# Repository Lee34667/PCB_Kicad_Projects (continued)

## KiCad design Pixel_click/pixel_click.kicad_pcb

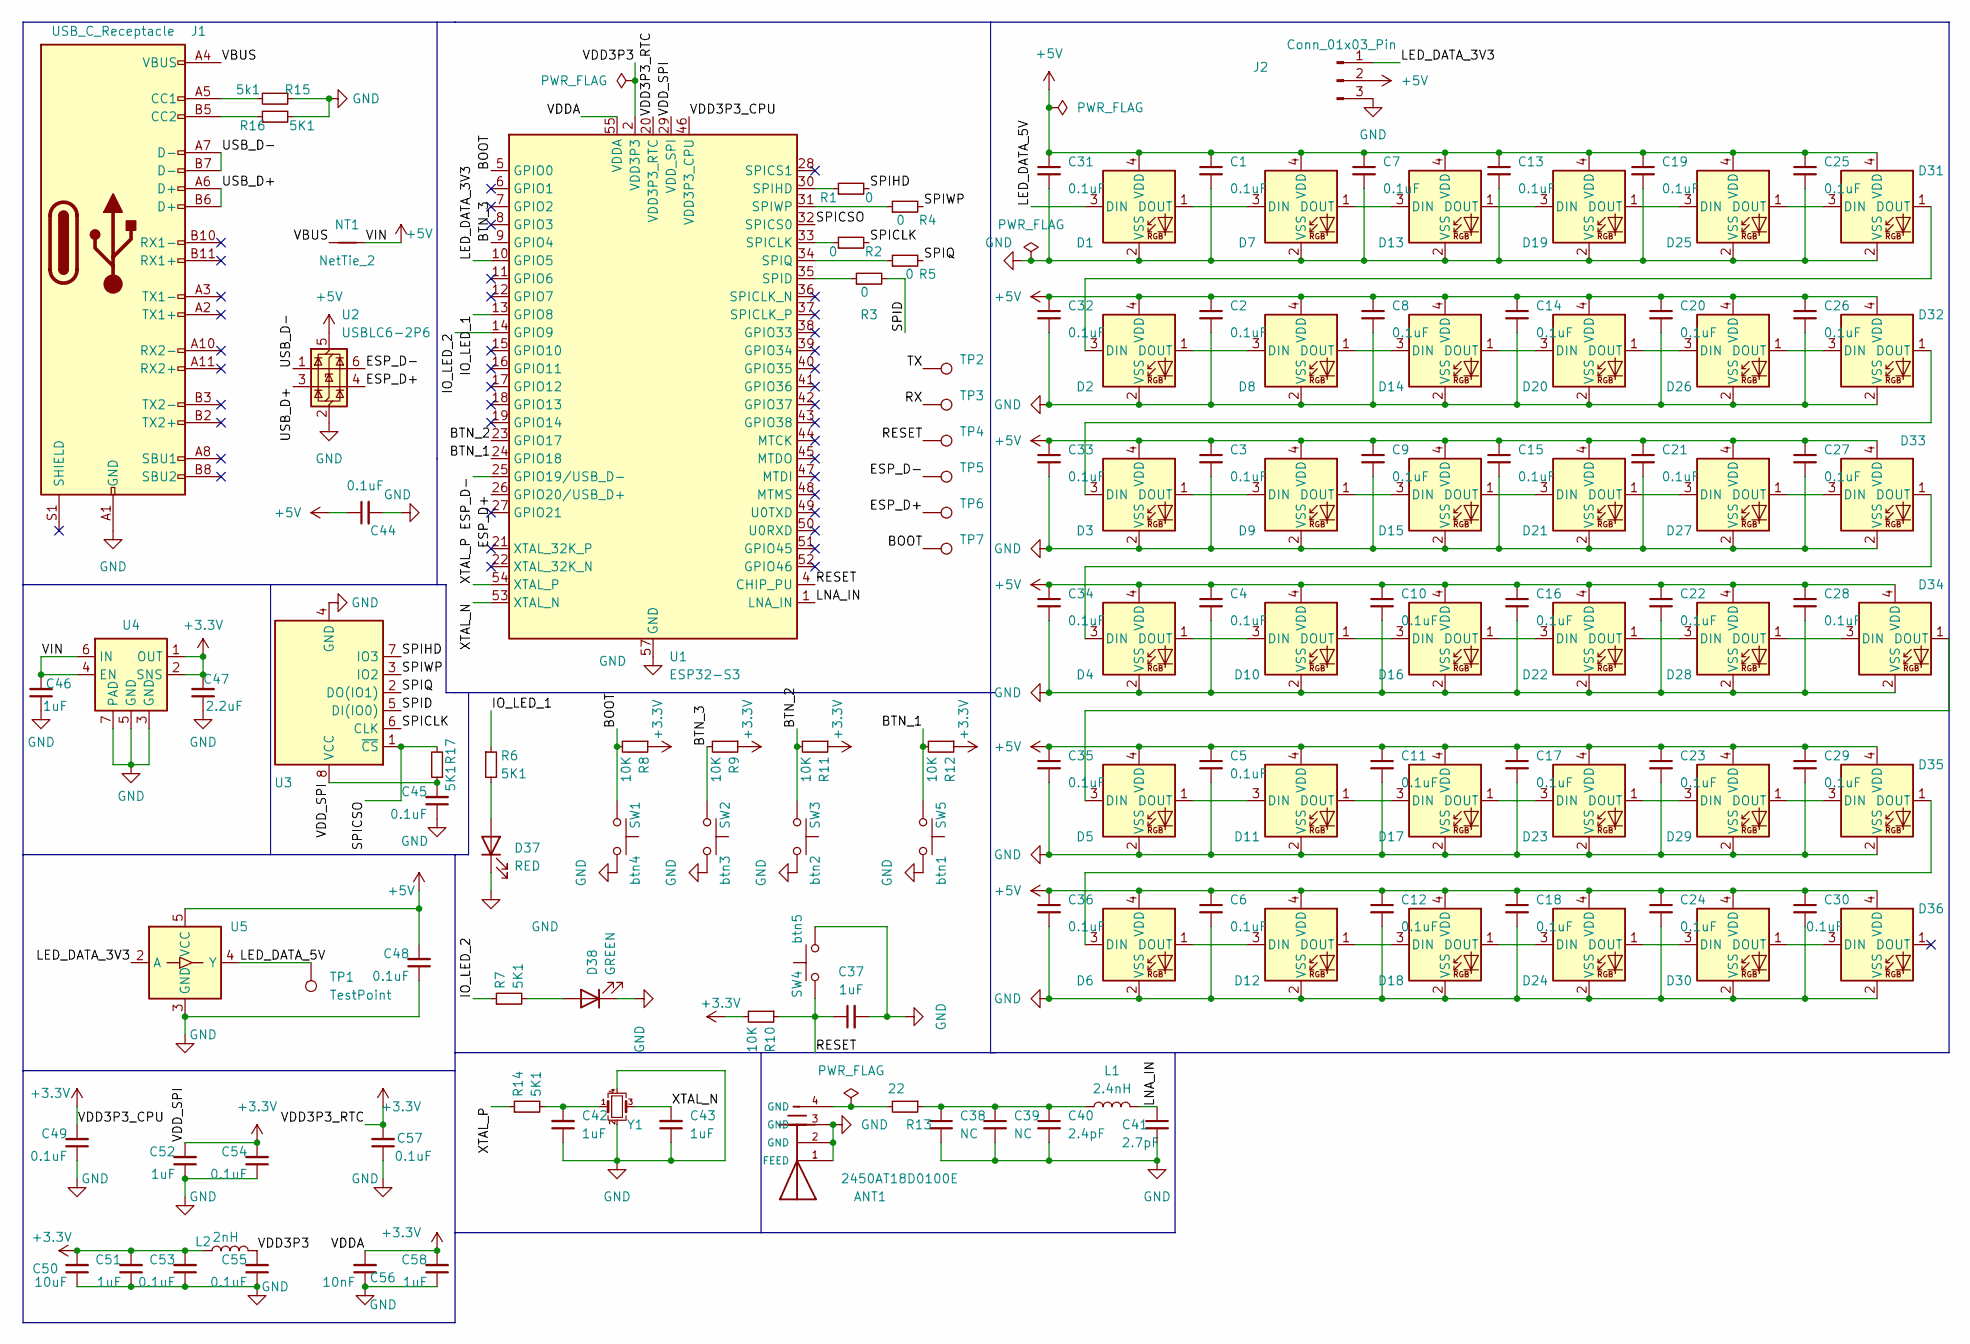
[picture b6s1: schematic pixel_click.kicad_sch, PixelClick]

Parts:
ANT1: 2450AT18D0100E; DFN320X160X120-4RN
C1, C2, C3, C4, C5, C6, C7, C8, C9, C10, C11, C12, C13, C14, C15, C16, C17, C18, C19, C20, C21, C22, C23, C24, C25, C26, C27, C28, C29, C30, C31, C32, C33, C34, C35, C36, C44, C45, C48, C49, C53, C54, C55, C57: 0.1uF; C_0201_0603Metric
C37, C42, C43, C46, C51, C52, C58: 1uF; C_0201_0603Metric
C38, C39: NC; C_0201_0603Metric
C40: 2.4pF; C_0201_0603Metric
C41: 2.7pF; C_0201_0603Metric
C47: 2.2uF; C_0201_0603Metric
C50: 10uF; C_0201_0603Metric
C56: 10nF; C_0201_0603Metric
D1, D2, D3, D4, D5, D6, D7, D8, D9, D10, D11, D12, D13, D14, D15, D16, D17, D18, D19, D20, D21, D22, D23, D24, D25, D26, D27, D28, D29, D30, D31, D32, D33, D34, D35, D36: SK6805; LED_SK6805_PLCC4_2.4x2.7mm_P1.3mm
D37: RED; LED_0201_0603Metric
D38: GREEN; LED_0402_1005Metric
J1: USB_C_Receptacle; USB_C_Receptacle_Amphenol_12401548E4-2A
J2: Conn_01x03_Pin; PinHeader_1x03_P1.27mm_Horizontal
L1: 2.4nH; L_0201_0603Metric
L2: 2nH; L_0201_0603Metric
NT1: NetTie_2; NetTie-2_SMD_Pad0.5mm
R1, R2, R3, R4, R5: 0; R_0201_0603Metric
R6, R7, R14, R16, R17: 5K1; R_0201_0603Metric
R8, R9, R10, R11, R12: 10K; R_0201_0603Metric
R13: 22; R_0201_0603Metric
R15: 5k1; R_0201_0603Metric
SW1: btn4; SW_Tactile_SPST_Angled_PTS645Vx39-2LFS
SW2: btn3; SW_Tactile_SPST_Angled_PTS645Vx39-2LFS
SW3: btn2; SW_Tactile_SPST_Angled_PTS645Vx39-2LFS
SW4: btn5; SW_Tactile_SPST_Angled_PTS645Vx39-2LFS
SW5: btn1; SW_Tactile_SPST_Angled_PTS645Vx39-2LFS
TP1: TestPoint; TestPoint_Bridge_Pitch2.0mm_Drill0.7mm
TP2, TP3, TP4, TP5, TP6, TP7: TestPoint
U1: ESP32-S3; QFN-56-1EP_7x7mm_P0.4mm_EP4x4mm
U2: USBLC6-2P6; SOT-666
U3: W25Q128JVS; SOIC-8_5.23x5.23mm_P1.27mm
U4: TLV76733DRVx; WSON-6-1EP_2x2mm_P0.65mm_EP1x1.6mm_ThermalVias
U5: SN74LV1T34DBV; SOT-23-5
Y1: Crystal_GND24_Small; XTAL_ECS-400-10-37B2-CKY-TR

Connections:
+3.3V: C45.2, C47.2, C49.2, C50.2, C51.2, C52.2, C53.2, C54.2, C56.2, C57.2, C58.2, L2.1, R8.1, R9.1, R10.2, R11.1, R12.1, R17.1, U1.20 (VDD3P3_RTC), U1.29 (VDD_SPI), U1.46 (VDD3P3_CPU), U1.55 (VDDA), U1.56 (VDDA), U3.8 (VCC), U4.1 (OUT), U4.2 (SNS)
+5V: C1.1, C2.1, C3.1, C4.1, C5.1, C6.1, C7.1, C8.1, C9.1, C10.1, C11.1, C12.1, C13.1, C14.1, C15.1, C16.1, C17.1, C18.1, C19.1, C20.1, C21.1, C22.1, C23.1, C24.1, C25.1, C26.1, C27.1, C28.1, C29.1, C30.1, C31.1, C32.1, C33.1, C34.1, C35.1, C36.1, C44.1, C46.2, C48.2, D1.4 (VDD), D2.4 (VDD), D3.4 (VDD), D4.4 (VDD), D5.4 (VDD), D6.4 (VDD), D7.4 (VDD), D8.4 (VDD), D9.4 (VDD), D10.4 (VDD), D11.4 (VDD), D12.4 (VDD), D13.4 (VDD), D14.4 (VDD), D15.4 (VDD), D16.4 (VDD), D17.4 (VDD), D18.4 (VDD), D19.4 (VDD), D20.4 (VDD), D21.4 (VDD), D22.4 (VDD), D23.4 (VDD), D24.4 (VDD), D25.4 (VDD), D26.4 (VDD), D27.4 (VDD), D28.4 (VDD), D29.4 (VDD), D30.4 (VDD), D31.4 (VDD), D32.4 (VDD), D33.4 (VDD), D34.4 (VDD), D35.4 (VDD), D36.4 (VDD), J2.2, NT1.2, U2.5 (VBUS), U4.4 (EN), U4.6 (IN), U5.5 (VCC)
/BOOT: R8.2, SW1.1, TP7.1, U1.5 (GPIO0)
/BTN_1: R12.2, SW5.1, U1.24 (GPIO18), U1.27 (GPIO18)
/BTN_2: R11.2, SW3.1, U1.23 (GPIO17)
/BTN_3: R9.2, SW2.1, U1.9 (GPIO4), U1.28 (GP1O4)
/ESP_D+: TP6.1, U1.26 (GPIO20/USB_D+), U2.4 (I/O2)
/ESP_D-: TP5.1, U1.25 (GPIO19/USB_D-), U2.6 (I/O1)
/IO_LED_1: R6.1, U1.13 (GPIO8)
/IO_LED_2: R7.1, U1.14 (GPIO9)
/LED_DATA_3V3: J2.1, U1.10 (GPIO5), U5.2 (A)
/LED_DATA_5V: D1.3 (DIN), TP1.1, U5.4 (Y)
/LNA_IN: C41.1, L1.2, U1.1 (LNA_IN)
/RESET: C37.1, R10.1, SW4.1, TP4.1, U1.4 (CHIP_PU)
/SPICLK: R2.2, U3.6 (CLK)
/SPICSO: R17.2, U1.32 (SPICS0), U3.1 (~CS)
/SPID: R3.2, U3.5 (DI(IO0))
/SPIHD: R1.2, U3.7 (IO3)
/SPIQ: R5.2, U3.2 (DO(IO1))
/SPIWP: R4.2, U3.3 (IO2)
/USB_D+: J1.A6 (D+), J1.B6 (D+), U2.3 (I/O2)
/USB_D-: J1.A7 (D-), J1.B7 (D-), U2.1 (I/O1)
/VBUS: J1.A4 (VBUS), J1.A9 (VBUS), J1.B4 (VBUS), J1.B9 (VBUS), NT1.1
/VDD3P3: C55.2, L2.2, U1.2 (VDD3P3), U1.3 (VDD3P3)
/XTAL_N: C43.2, U1.53 (XTAL_N), Y1.3
/XTAL_P: R14.1, U1.54 (XTAL_P)
GND: ANT1.1 (FEED), ANT1.2 (GND), ANT1.3 (GND), C1.2, C2.2, C3.2, C4.2, C5.2, C6.2, C7.2, C8.2, C9.2, C10.2, C11.2, C12.2, C13.2, C14.2, C15.2, C16.2, C17.2, C18.2, C19.2, C20.2, C21.2, C22.2, C23.2, C24.2, C25.2, C26.2, C27.2, C28.2, C29.2, C30.2, C31.2, C32.2, C33.2, C34.2, C35.2, C36.2, C37.2, C38.2, C39.2, C40.2, C41.2, C42.1, C43.1, C44.2, C45.1, C46.1, C47.1, C48.1, C49.1, C50.1, C51.1, C52.1, C53.1, C54.1, C55.1, C56.1, C57.1, C58.1, D1.2 (VSS), D2.2 (VSS), D3.2 (VSS), D4.2 (VSS), D5.2 (VSS), D6.2 (VSS), D7.2 (VSS), D8.2 (VSS), D9.2 (VSS), D10.2 (VSS), D11.2 (VSS), D12.2 (VSS), D13.2 (VSS), D14.2 (VSS), D15.2 (VSS), D16.2 (VSS), D17.2 (VSS), D18.2 (VSS), D19.2 (VSS), D20.2 (VSS), D21.2 (VSS), D22.2 (VSS), D23.2 (VSS), D24.2 (VSS), D25.2 (VSS), D26.2 (VSS), D27.2 (VSS), D28.2 (VSS), D29.2 (VSS), D30.2 (VSS), D31.2 (VSS), D32.2 (VSS), D33.2 (VSS), D34.2 (VSS), D35.2 (VSS), D36.2 (VSS), D37.1 (K), D38.1 (K), J1.A1 (GND), J1.A12 (GND), J1.B1 (GND), J1.B12 (GND), J2.3, R15.1, R16.2, SW1.2, SW2.2, SW3.2, SW4.2, SW5.2, U1.57 (GND), U2.2 (GND), U3.4 (GND), U4.3 (GND), U4.5 (GND), U4.7 (PAD), U5.3 (GND), Y1.2, Y1.4
unnamed: ANT1.4 (GND), R13.2
unnamed: C38.1, C39.1, C40.1, L1.1, R13.1
unnamed: C42.2, R14.2, Y1.1
unnamed: D1.1 (DOUT), D7.3 (DIN)
unnamed: D2.3 (DIN), D31.1 (DOUT)
unnamed: D2.1 (DOUT), D8.3 (DIN)
unnamed: D3.3 (DIN), D32.1 (DOUT)
unnamed: D3.1 (DOUT), D9.3 (DIN)
unnamed: D4.1 (DOUT), D10.3 (DIN)
unnamed: D10.1 (DOUT), D16.3 (DIN)
unnamed: D5.1 (DOUT), D11.3 (DIN)
unnamed: D11.1 (DOUT), D17.3 (DIN)
unnamed: D6.1 (DOUT), D12.3 (DIN)
unnamed: D12.1 (DOUT), D18.3 (DIN)
unnamed: D7.1 (DOUT), D13.3 (DIN)
unnamed: D13.1 (DOUT), D19.3 (DIN)
unnamed: D8.1 (DOUT), D14.3 (DIN)
unnamed: D14.1 (DOUT), D20.3 (DIN)
unnamed: D9.1 (DOUT), D15.3 (DIN)
unnamed: D15.1 (DOUT), D21.3 (DIN)
unnamed: D16.1 (DOUT), D22.3 (DIN)
unnamed: D17.1 (DOUT), D23.3 (DIN)
unnamed: D18.1 (DOUT), D24.3 (DIN)
unnamed: D19.1 (DOUT), D25.3 (DIN)
unnamed: D20.1 (DOUT), D26.3 (DIN)
unnamed: D21.1 (DOUT), D27.3 (DIN)
unnamed: D22.1 (DOUT), D28.3 (DIN)
unnamed: D23.1 (DOUT), D29.3 (DIN)
unnamed: D24.1 (DOUT), D30.3 (DIN)
unnamed: D25.1 (DOUT), D31.3 (DIN)
unnamed: D26.1 (DOUT), D32.3 (DIN)
unnamed: D27.1 (DOUT), D33.3 (DIN)
unnamed: D28.1 (DOUT), D34.3 (DIN)
unnamed: D29.1 (DOUT), D35.3 (DIN)
unnamed: D30.1 (DOUT), D36.3 (DIN)
unnamed: D4.3 (DIN), D33.1 (DOUT)
unnamed: D5.3 (DIN), D34.1 (DOUT)
unnamed: D6.3 (DIN), D35.1 (DOUT)
unnamed: D37.2 (A), R6.2
unnamed: D38.2 (A), R7.2
unnamed: J1.A5 (CC1), R15.2
unnamed: J1.B5 (CC2), R16.1
unnamed: R2.1, U1.33 (SPICLK)
unnamed: R3.1, U1.35 (SPID)
unnamed: R1.1, U1.30 (SPIHD)
unnamed: R5.1, U1.34 (SPIQ)
unnamed: R4.1, U1.31 (SPIWP)

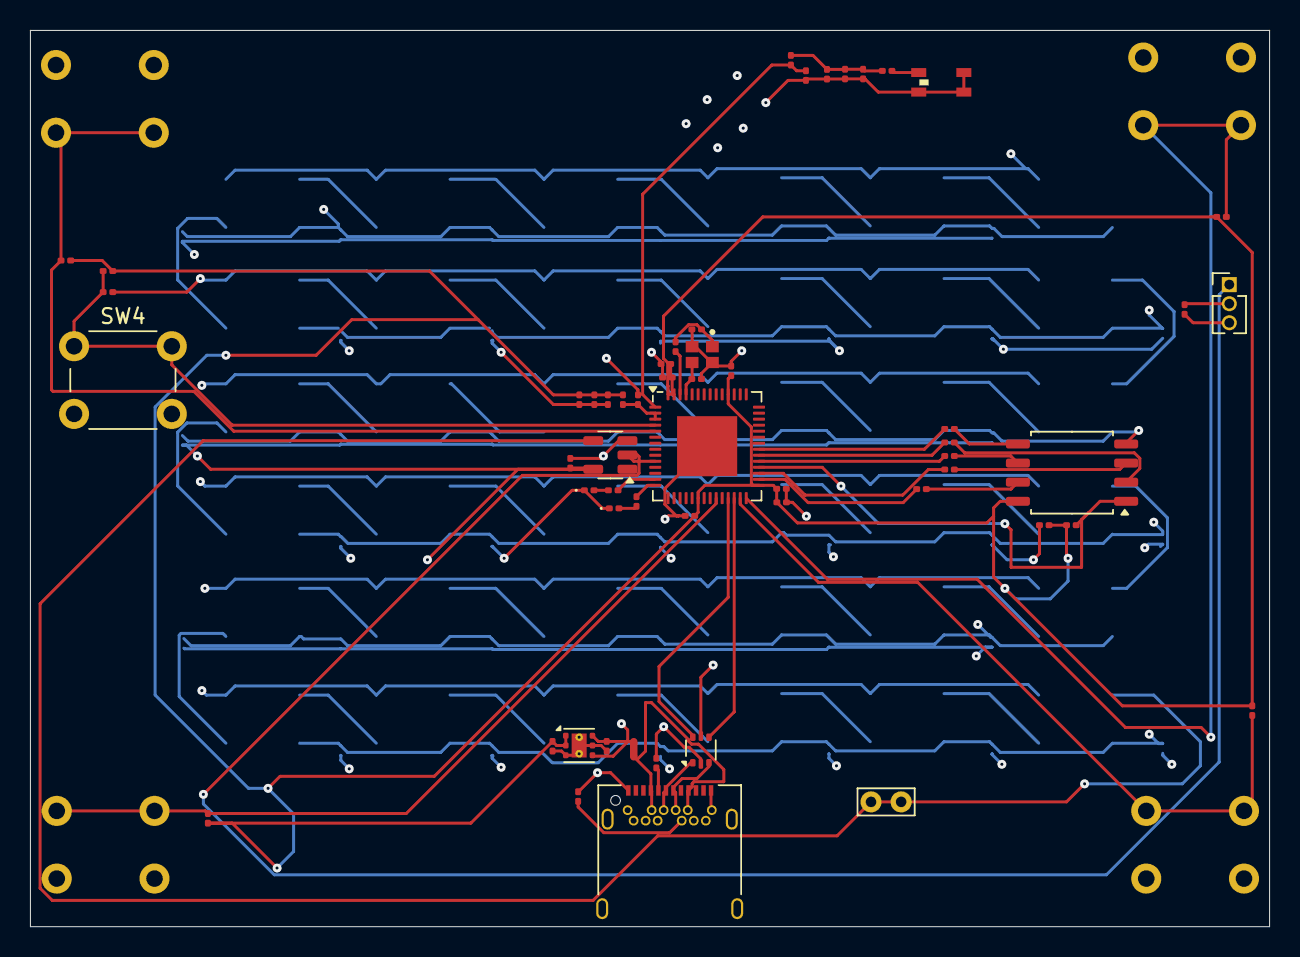
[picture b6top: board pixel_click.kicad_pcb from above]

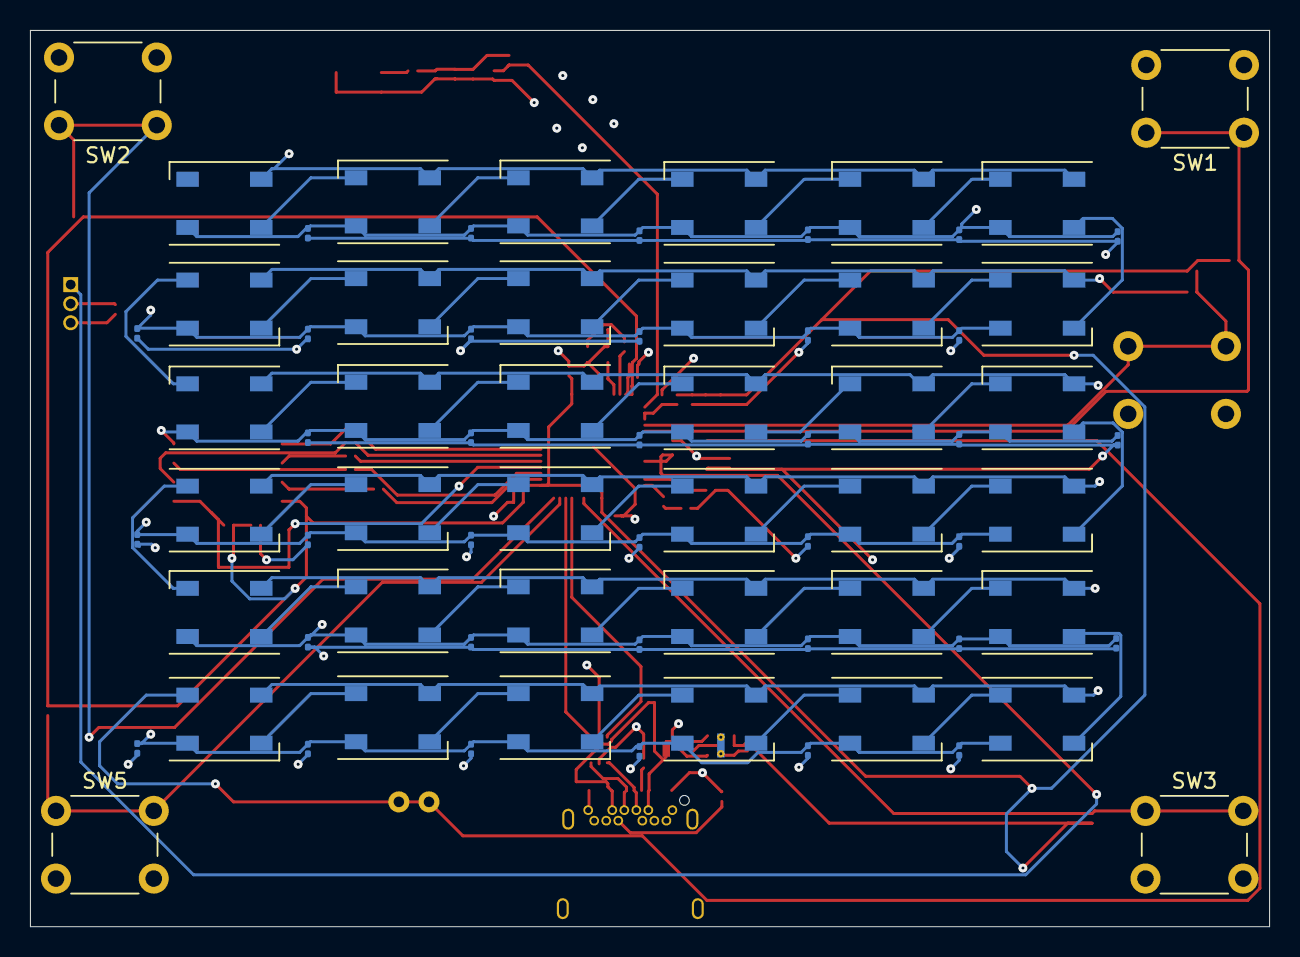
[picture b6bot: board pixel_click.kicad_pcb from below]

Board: 4 copper layers, 82.4 x 59.6 mm, 131 parts (76 on the bottom side), 74 nets.

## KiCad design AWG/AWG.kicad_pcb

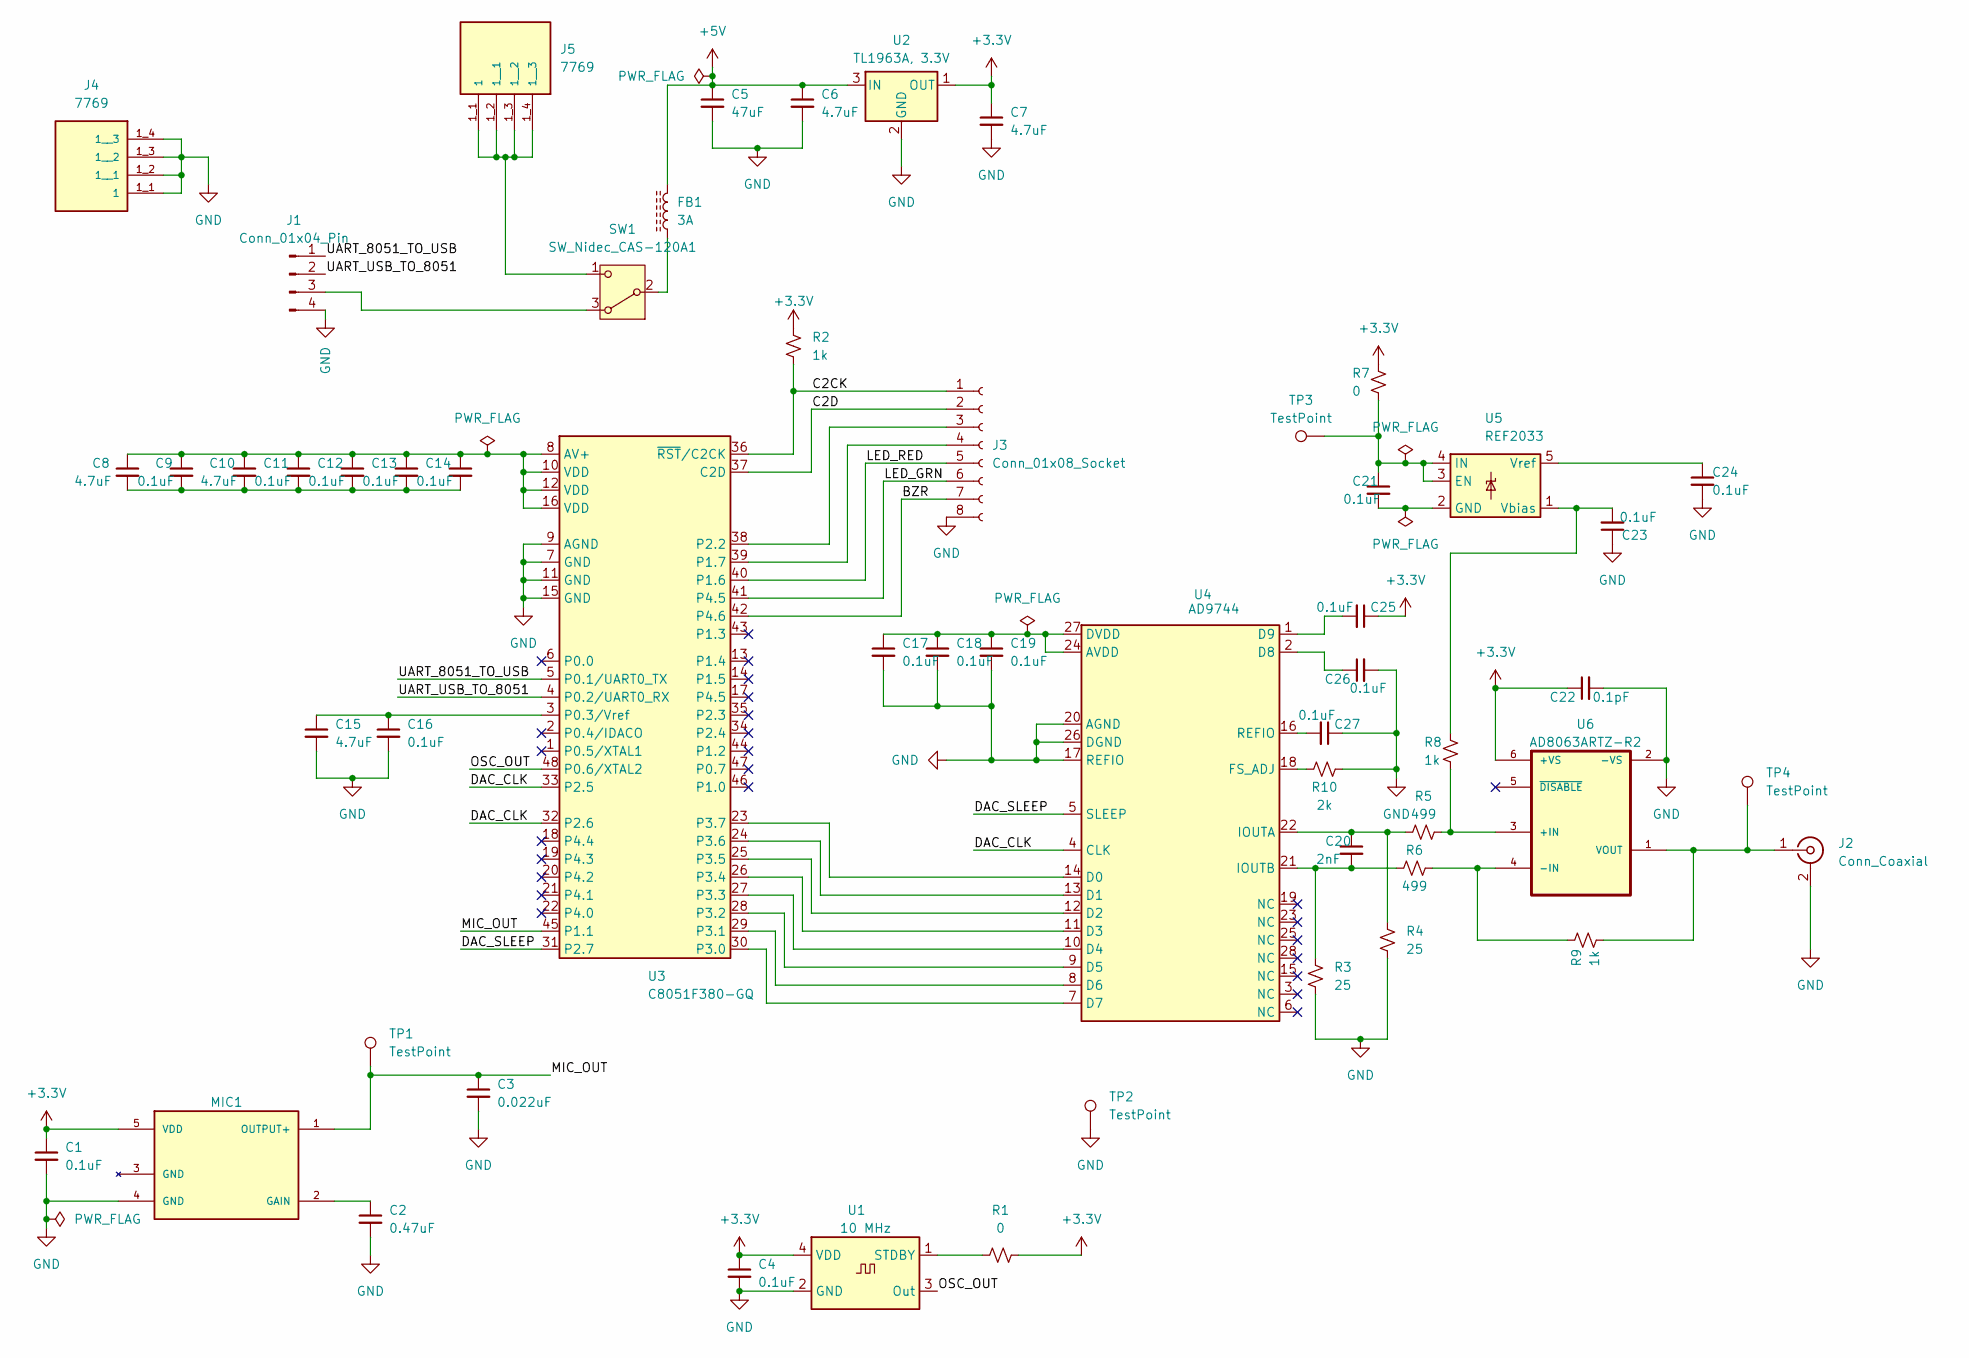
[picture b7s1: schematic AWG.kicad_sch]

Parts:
C1, C4, C9, C11, C12, C13, C14, C16, C17, C18, C19, C21, C23, C24, C25, C26, C27: 0.1uF; C_0805_2012Metric
C2: 0.47uF; C_0805_2012Metric
C3: 0.022uF; C_0805_2012Metric
C5: 47uF; CP_EIA-3528-12_Kemet-T
C6: 4.7uF; CP_EIA-3528-12_Kemet-T
C7, C8, C10, C15: 4.7uF; C_0805_2012Metric
C20: 2nF; C_0805_2012Metric
C22: 0.1pF; C_0805_2012Metric
FB1: 3A; L_Ferrocore_DLG-0302
J1: Conn_01x04_Pin; PinHeader_1x04_P2.00mm_Horizontal
J2: Conn_Coaxial; SMB_Jack_Vertical
J3: Conn_01x08_Socket; PinSocket_1x08_P2.00mm_Horizontal
J4, J5: 7769; KEYSTONE_7769; PARTREV B
MIC1: ICS-40618; MIC_ICS-40618
R1, R7: 0; R_0603_1608Metric_Pad0.98x0.95mm_HandSolder
R2, R8, R9: 1k; R_0603_1608Metric_Pad0.98x0.95mm_HandSolder
R3, R4: 25; R_0603_1608Metric_Pad0.98x0.95mm_HandSolder
R5, R6: 499; R_0603_1608Metric_Pad0.98x0.95mm_HandSolder
R10: 2k; R_0603_1608Metric_Pad0.98x0.95mm_HandSolder
SW1: SW_Nidec_CAS-120A1; Nidec_Copal_CAS-120A
TP1, TP2, TP3, TP4: TestPoint; TestPoint_Loop_D2.50mm_Drill1.0mm
U1: 10 MHz; Oscillator_SMD_Abracon_ASDMB-4Pin_2.5x2.0mm
U2: TL1963A, 3.3V; SOT-89-3
U3: C8051F380-GQ; TQFP-48_7x7mm_P0.5mm
U4: AD9744; TSSOP-28_4.4x9.7mm_P0.65mm
U5: REF2033; SOT-23-5
U6: AD8063ARTZ-R2; SOT95P280X145-6

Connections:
+3.3V: C1.1, C4.1, C7.1, C22.1, C25.1, MIC1.5 (VDD), R1.2, R2.1, R7.1, U1.4 (VDD), U2.1 (OUT), U6.6 (+VS)
+5V: C5.1, C6.1, FB1.2, U2.3 (IN)
/BZR: J3.7, U3.42 (P4.6)
/C2CK: J3.1, R2.2, U3.36 (~RST/C2CK)
/C2D: J3.2, U3.37 (C2D)
/DAC_CLK: U3.32 (P2.6), U3.33 (P2.5), U4.4 (CLK)
/DAC_SLEEP: U3.31 (P2.7), U4.5 (SLEEP)
/LED_GRN: J3.6, U3.41 (P4.5)
/LED_RED: J3.5, U3.40 (P1.6)
/MIC_OUT: C3.1, MIC1.1 (OUTPUT+), TP1.1, U3.45 (P1.1)
/OSC_OUT: U1.3 (Out), U3.48 (P0.6/XTAL2)
/UART_8051_TO_USB: J1.1, U3.5 (P0.1/UART0_TX)
/UART_USB_TO_8051: J1.2, U3.4 (P0.2/UART0_RX)
GND: C1.2, C2.2, C3.2, C4.2, C5.2, C6.2, C7.2, C15.2, C16.2, C17.2, C18.2, C19.2, C22.2, C23.1, C24.2, C26.2, C27.1, J1.4, J2.2 (Ext), J3.8, J4.1_1 (1), J4.1_2 (1__1), J4.1_3 (1__2), J4.1_4 (1__3), MIC1.4 (GND), R3.2, R4.2, R10.1, TP2.1, U1.2 (GND), U2.2 (GND), U3.7 (GND), U3.9 (AGND), U3.11 (GND), U3.15 (GND), U4.17 (REFIO), U4.20 (AGND), U4.26 (DGND), U6.2 (-VS)
unnamed: C8.2, C9.2, C10.2, C11.2, C12.2, C13.2, C14.2
unnamed: C27.2, U4.16 (REFIO)
unnamed: J1.3, SW1.3 (A)
unnamed: J2.1 (In), R9.2, TP4.1, U6.1 (VOUT)
unnamed: J3.3, U3.38 (P2.2)
unnamed: J3.4, U3.39 (P1.7)
unnamed: J5.1_1 (1), J5.1_2 (1__1), J5.1_3 (1__2), J5.1_4 (1__3), SW1.1 (C)
unnamed: C2.1, MIC1.2 (GAIN)
unnamed: FB1.1, SW1.2 (B)
unnamed: R1.1, U1.1 (STDBY)
unnamed: C8.1, C9.1, C10.1, C11.1, C12.1, C13.1, C14.1, U3.8 (AV+), U3.10 (VDD), U3.12 (VDD), U3.16 (VDD)
unnamed: C15.1, C16.1, U3.3 (P0.3/Vref)
unnamed: U3.30 (P3.0), U4.7 (D7)
unnamed: U3.29 (P3.1), U4.8 (D6)
unnamed: U3.28 (P3.2), U4.9 (D5)
unnamed: U3.27 (P3.3), U4.10 (D4)
unnamed: U3.26 (P3.4), U4.11 (D3)
unnamed: U3.25 (P3.5), U4.12 (D2)
unnamed: U3.24 (P3.6), U4.13 (D1)
unnamed: U3.23 (P3.7), U4.14 (D0)
unnamed: C17.1, C18.1, C19.1, U4.24 (AVDD), U4.27 (DVDD)
unnamed: C26.1, U4.2 (D8)
unnamed: C25.2, U4.1 (D9)
unnamed: R10.2, U4.18 (FS_ADJ)
unnamed: C20.1, R4.1, R5.1, U4.22 (IOUTA)
unnamed: C20.2, R3.1, R6.1, U4.21 (IOUTB)
unnamed: C21.1, R7.2, TP3.1, U5.3 (EN), U5.4 (IN)
unnamed: C21.2, U5.2 (GND)
unnamed: C23.2, R8.1, U5.1 (Vbias)
unnamed: C24.1, U5.5 (Vref)
unnamed: R5.2, R8.2, U6.3 (+IN)
unnamed: R6.2, R9.1, U6.4 (-IN)

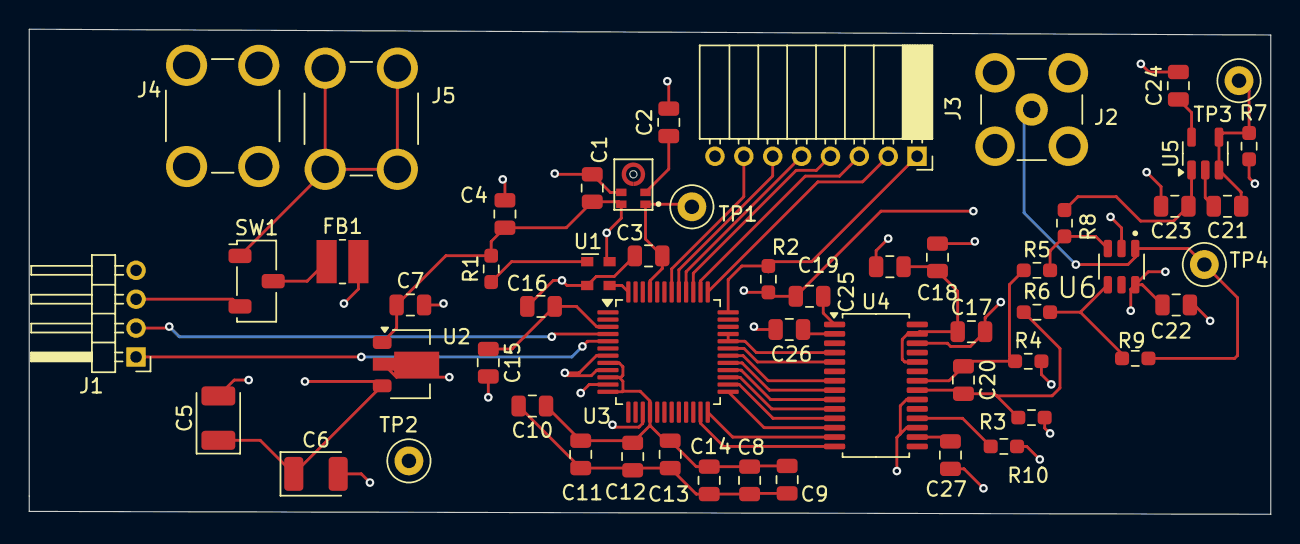
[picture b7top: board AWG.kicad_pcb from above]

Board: 4 copper layers, 86.0 x 33.6 mm, 55 parts (0 on the bottom side), 46 nets.

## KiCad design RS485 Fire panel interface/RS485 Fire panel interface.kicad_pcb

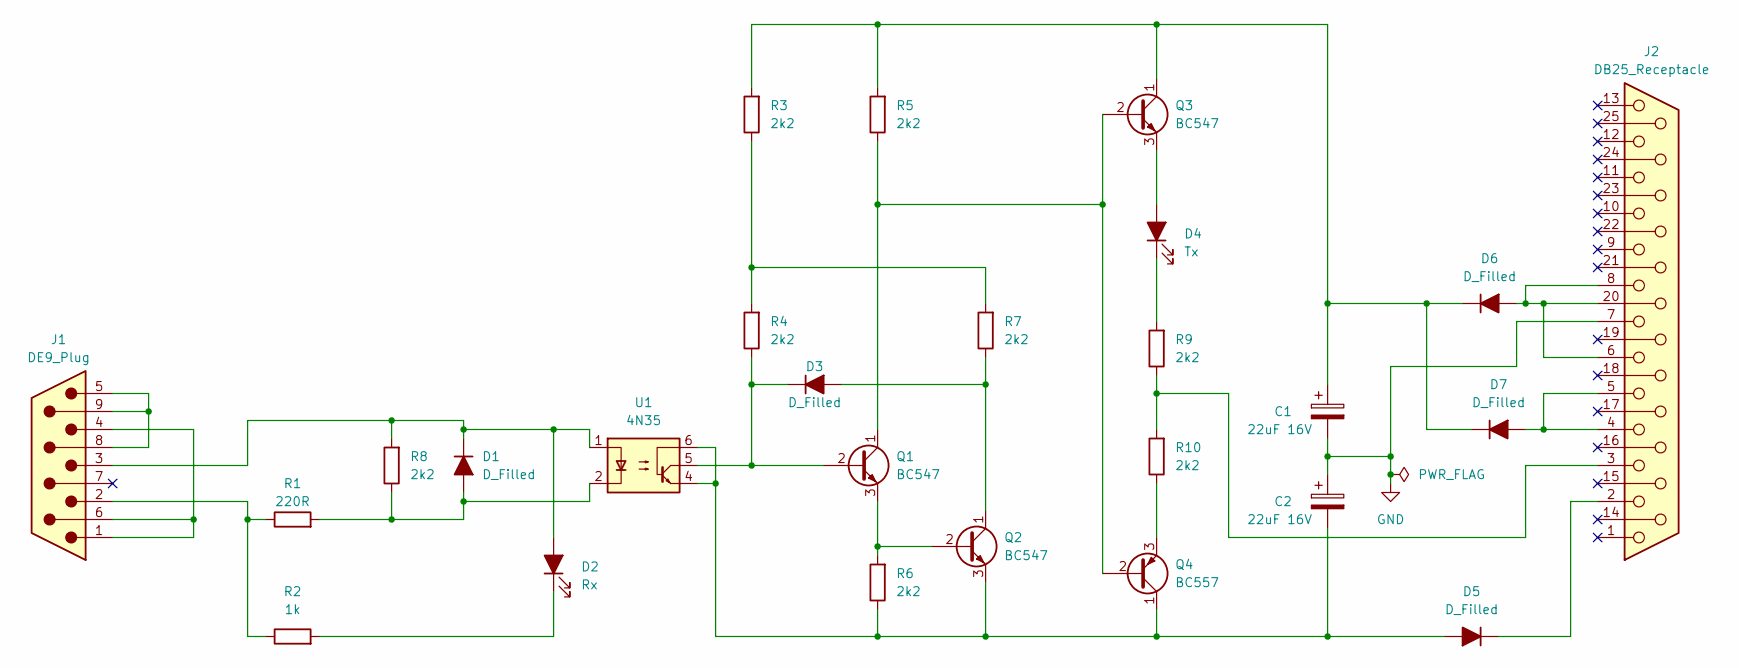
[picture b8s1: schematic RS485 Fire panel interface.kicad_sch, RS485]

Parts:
C1, C2: 22uF 16V; C_Rect_L4.6mm_W2.0mm_P2.50mm_MKS02_FKP02
D1, D3, D5, D6, D7: D_Filled; D_T-1_P10.16mm_Horizontal
D2: Rx; LED_D3.0mm_Horizontal_O1.27mm_Z2.0mm
D4: Tx; LED_D3.0mm_Horizontal_O1.27mm_Z2.0mm
J1: DE9_Plug; DSUB-9_Male_Horizontal_P2.77x2.54mm_EdgePinOffset9.40mm
J2: DB25_Receptacle; DSUB-25_Male_Horizontal_P2.77x2.54mm_EdgePinOffset9.40mm
Q1, Q2, Q3: BC547; TO-92_Inline
Q4: BC557; TO-92_Inline
R1: 220R; R_Axial_DIN0207_L6.3mm_D2.5mm_P10.16mm_Horizontal
R2: 1k; R_Axial_DIN0207_L6.3mm_D2.5mm_P10.16mm_Horizontal
R3, R4, R5, R6, R7, R8, R9, R10: 2k2; R_Axial_DIN0207_L6.3mm_D2.5mm_P10.16mm_Horizontal
U1: 4N35; DIP-6_W7.62mm

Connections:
GND: C1.2, C2.1, J2.7
unnamed: D1.2 (A), R1.2, R8.1, U1.2
unnamed: D1.1 (K), D2.2 (A), J1.3, R8.2, U1.1
unnamed: D2.1 (K), R2.2
unnamed: D3.2 (A), Q2.1 (C), R7.1
unnamed: D3.1 (K), Q1.2 (B), R4.1, U1.5
unnamed: D4.2 (A), Q3.3 (E)
unnamed: D4.1 (K), R9.2
unnamed: C2.2, D5.2 (A), Q2.3 (E), Q4.1 (C), R6.1, U1.4, U1.6
unnamed: D5.1 (K), J2.2
unnamed: D6.2 (A), J2.6, J2.8, J2.20
unnamed: C1.1, D6.1 (K), D7.1 (K), Q3.1 (C), R3.2, R5.2
unnamed: D7.2 (A), J2.4, J2.5
unnamed: J1.1, J1.4, J1.6
unnamed: J1.2, R1.1, R2.1
unnamed: J1.5, J1.8, J1.9
unnamed: J2.3, R9.1, R10.2
unnamed: Q1.1 (C), Q3.2 (B), Q4.2 (B), R5.1
unnamed: Q1.3 (E), Q2.2 (B), R6.2
unnamed: Q4.3 (E), R10.1
unnamed: R3.1, R4.2, R7.2

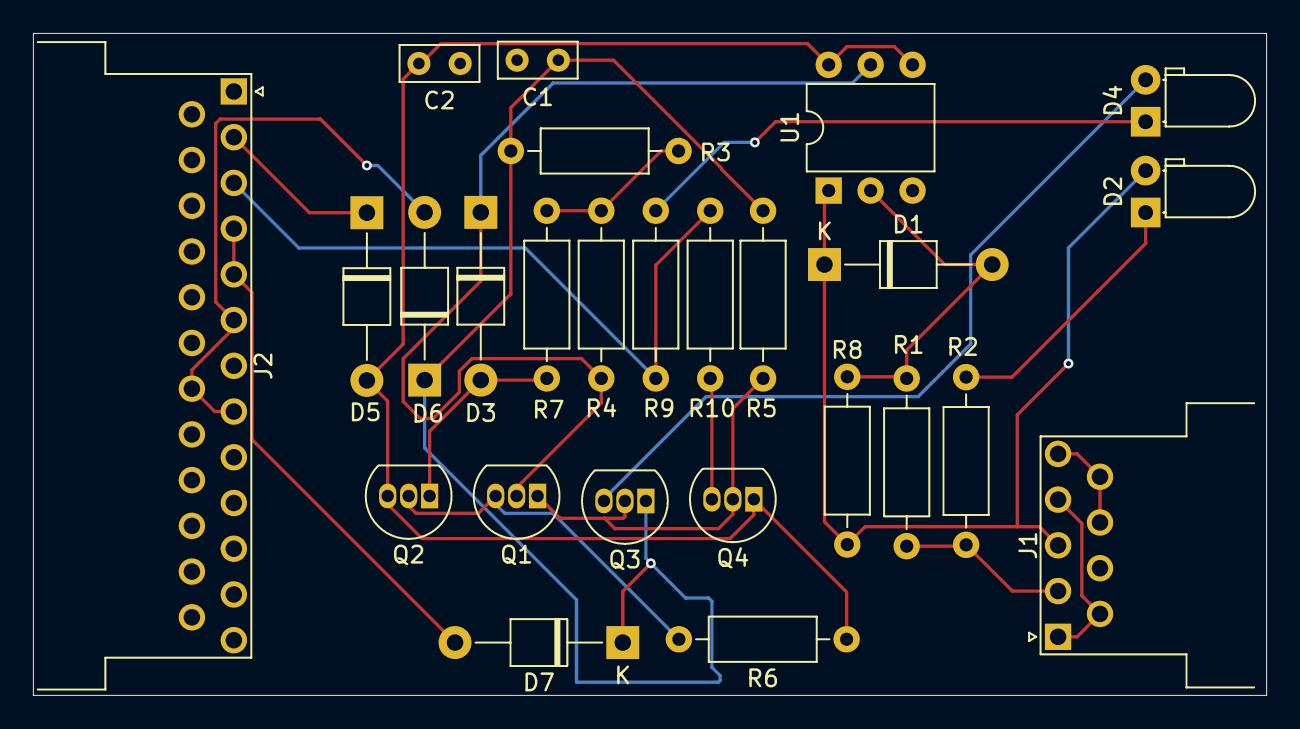
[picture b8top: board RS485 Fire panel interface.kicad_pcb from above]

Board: 2 copper layers, 74.7 x 40.1 mm, 26 parts (0 on the bottom side), 21 nets.

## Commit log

2024-07-18 Add files via upload
    In this 3 Transistors Audio Amplifier Circuit, first, the audio signal is fed into the circuit through mic 1. It is then converted into a tiny electrical signal that is sent to Q1. First, to amplify 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
    Application Uses:
    In mic, speaker audio applications.
2024-07-19 Create I wrote a blog about it !
